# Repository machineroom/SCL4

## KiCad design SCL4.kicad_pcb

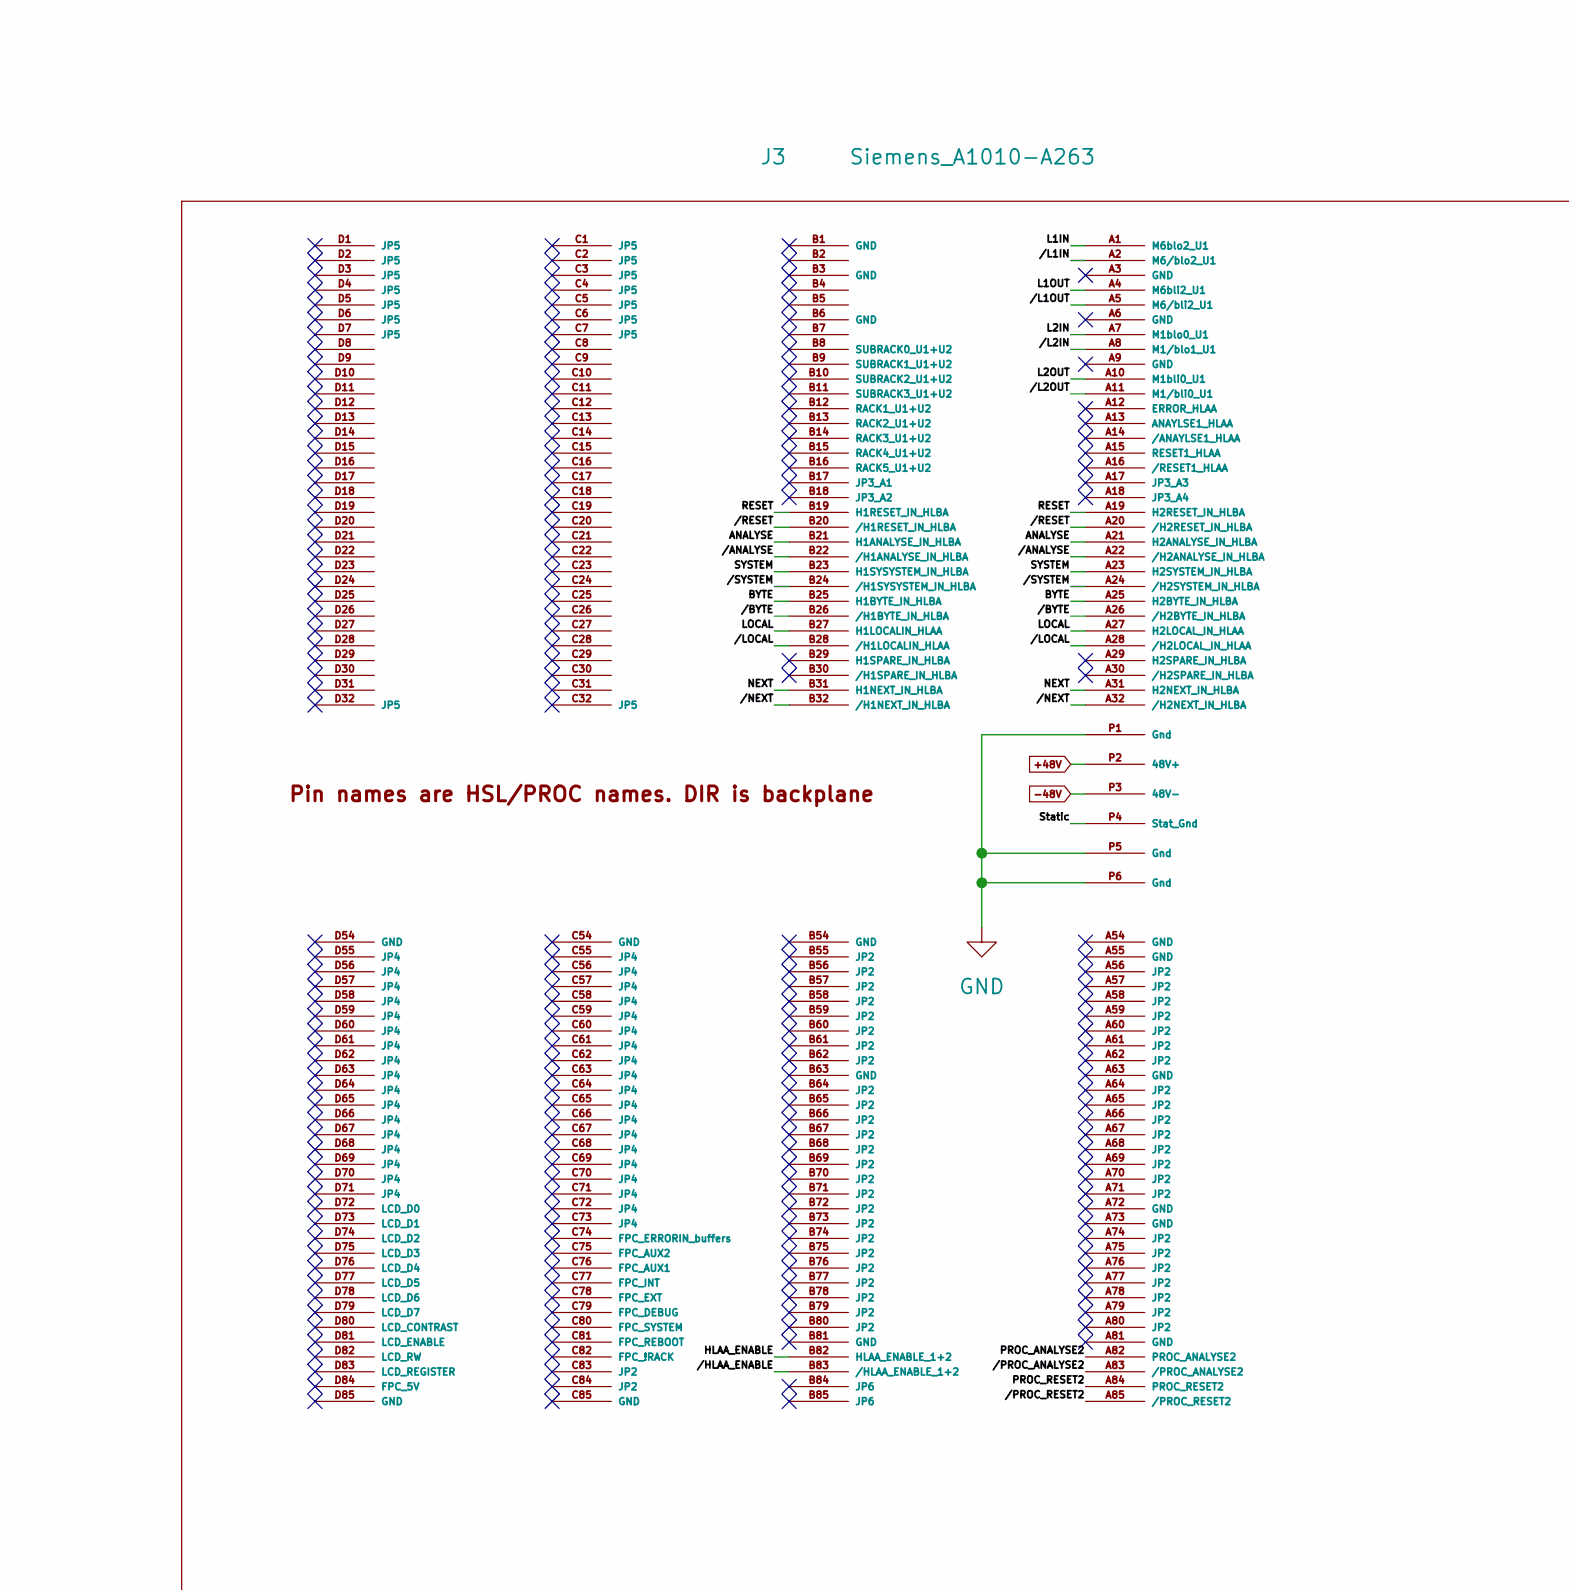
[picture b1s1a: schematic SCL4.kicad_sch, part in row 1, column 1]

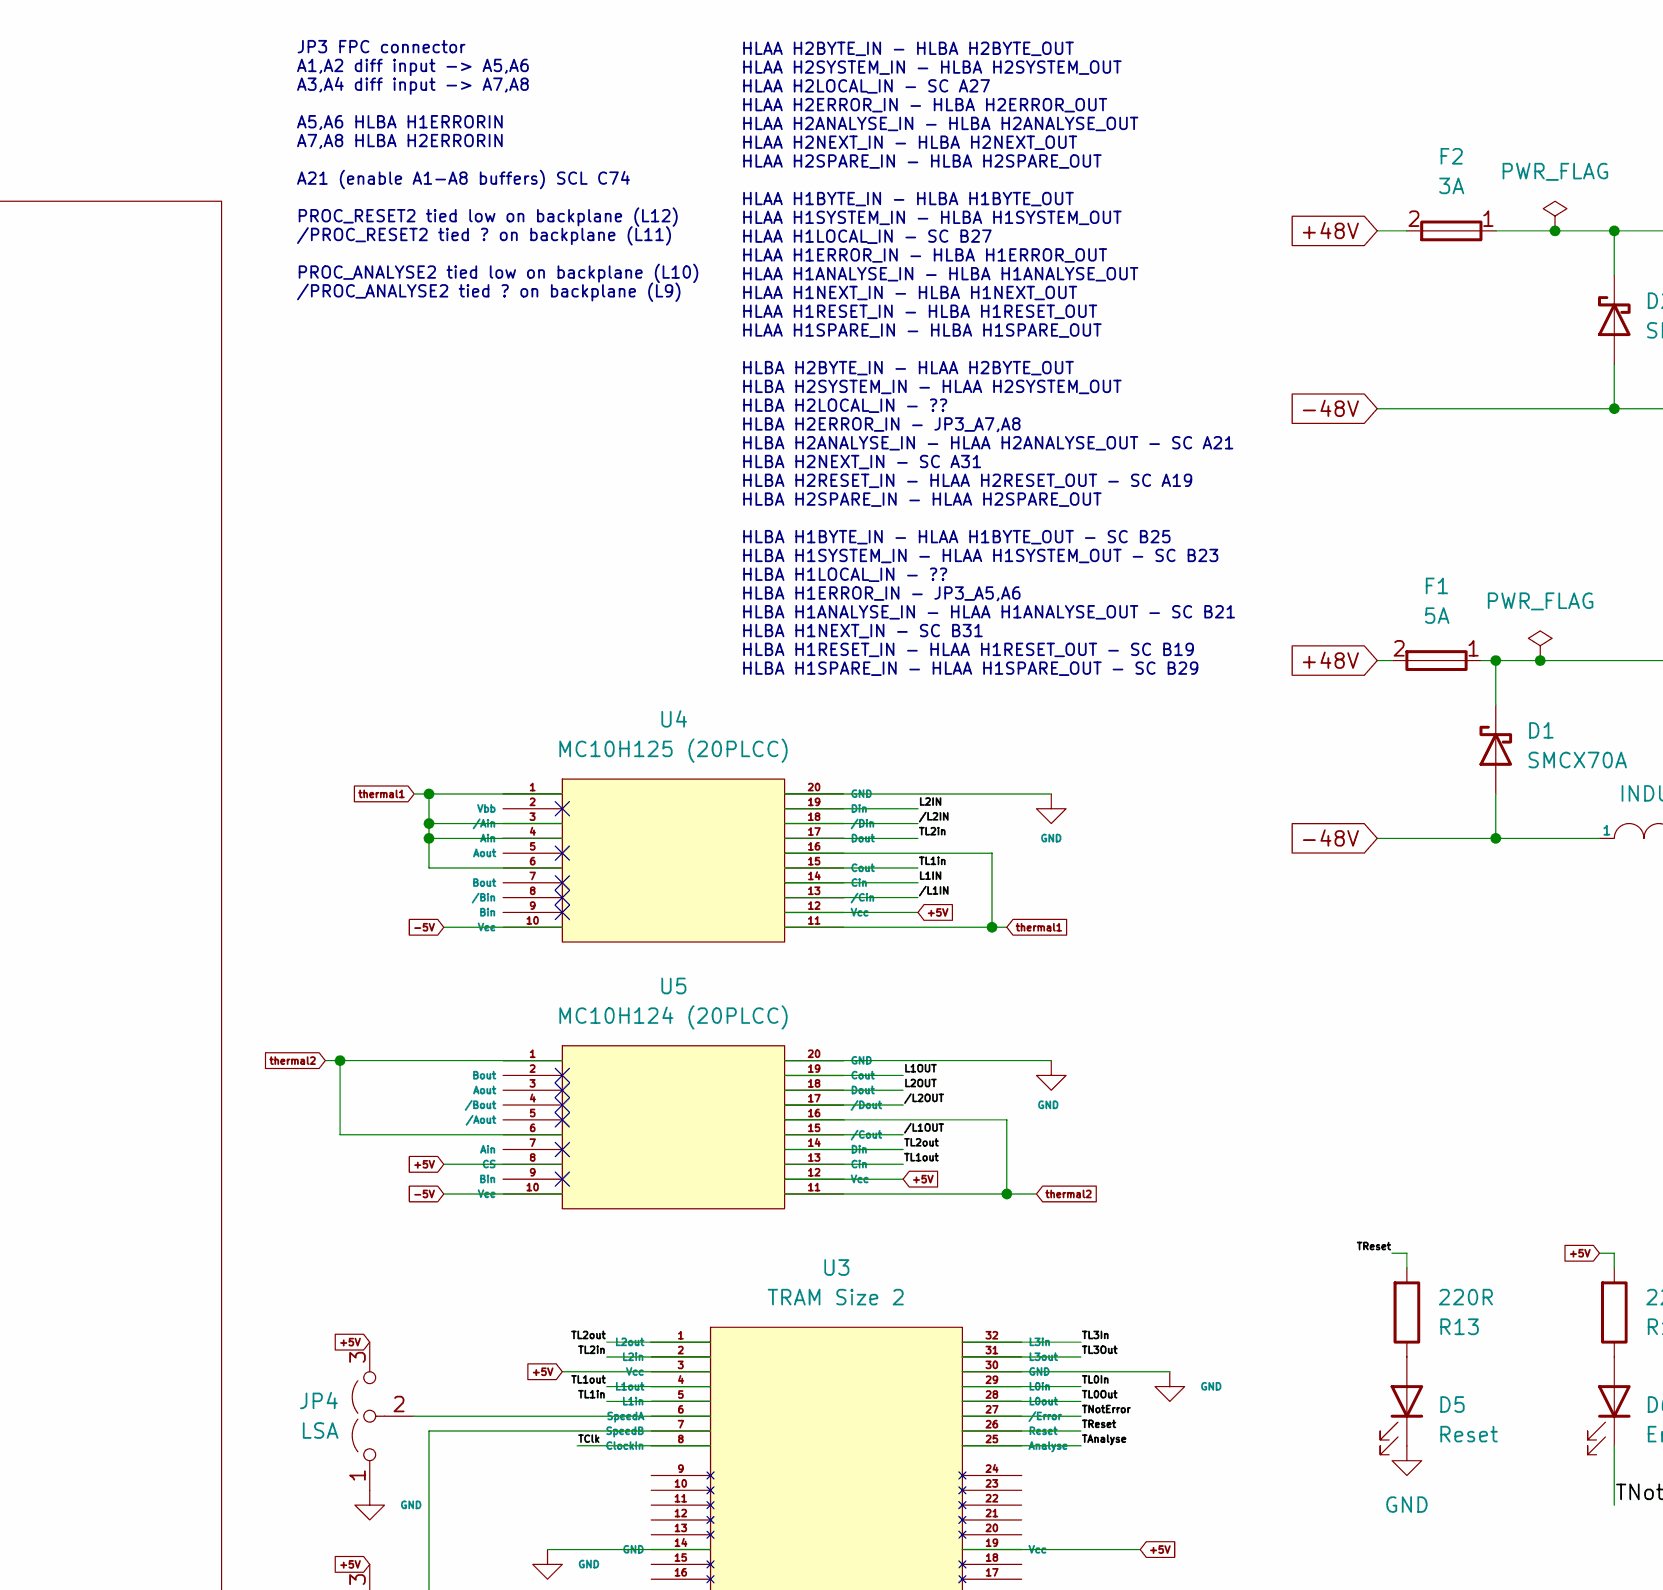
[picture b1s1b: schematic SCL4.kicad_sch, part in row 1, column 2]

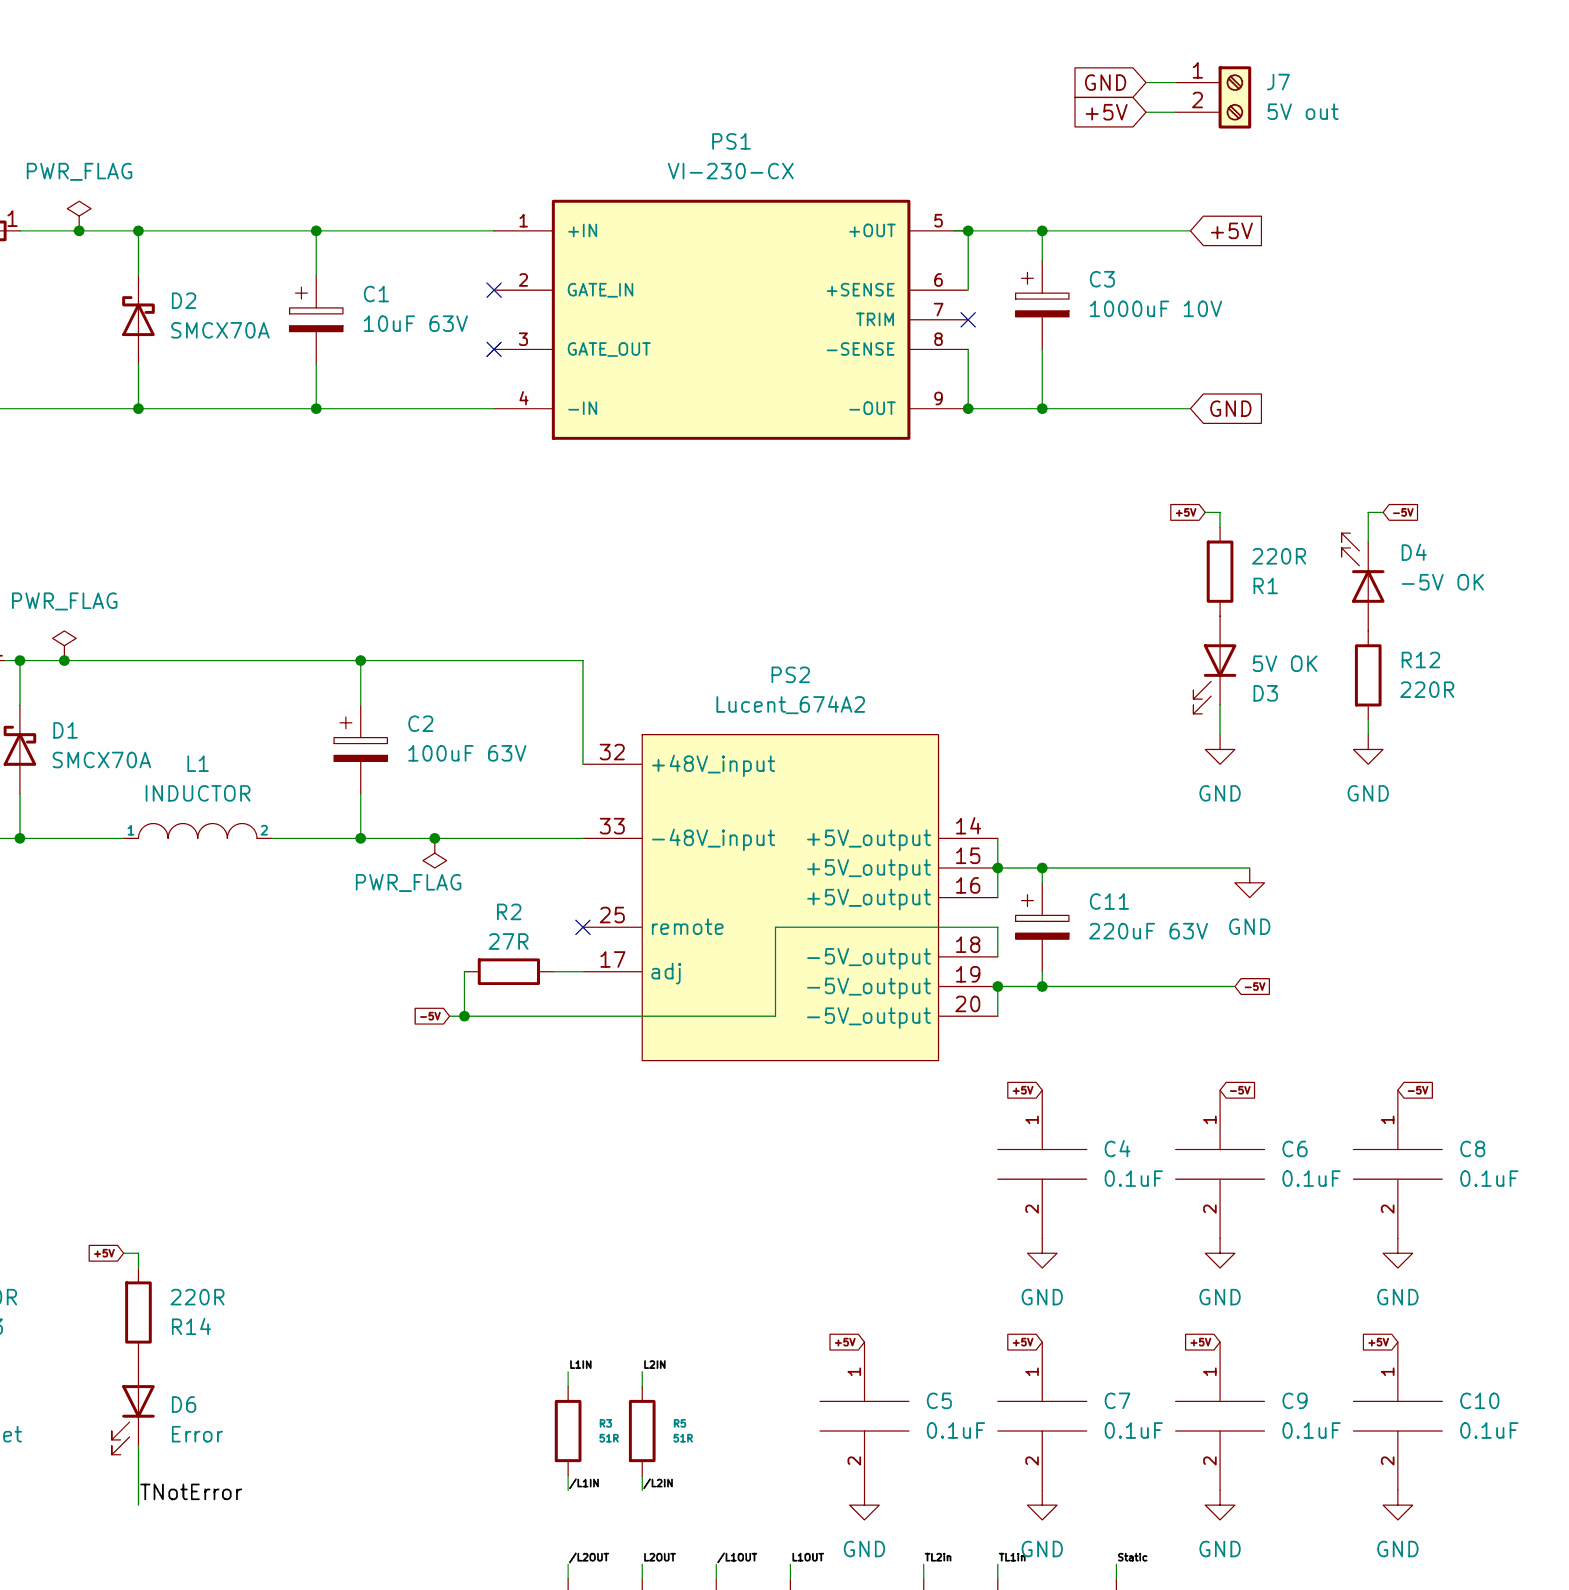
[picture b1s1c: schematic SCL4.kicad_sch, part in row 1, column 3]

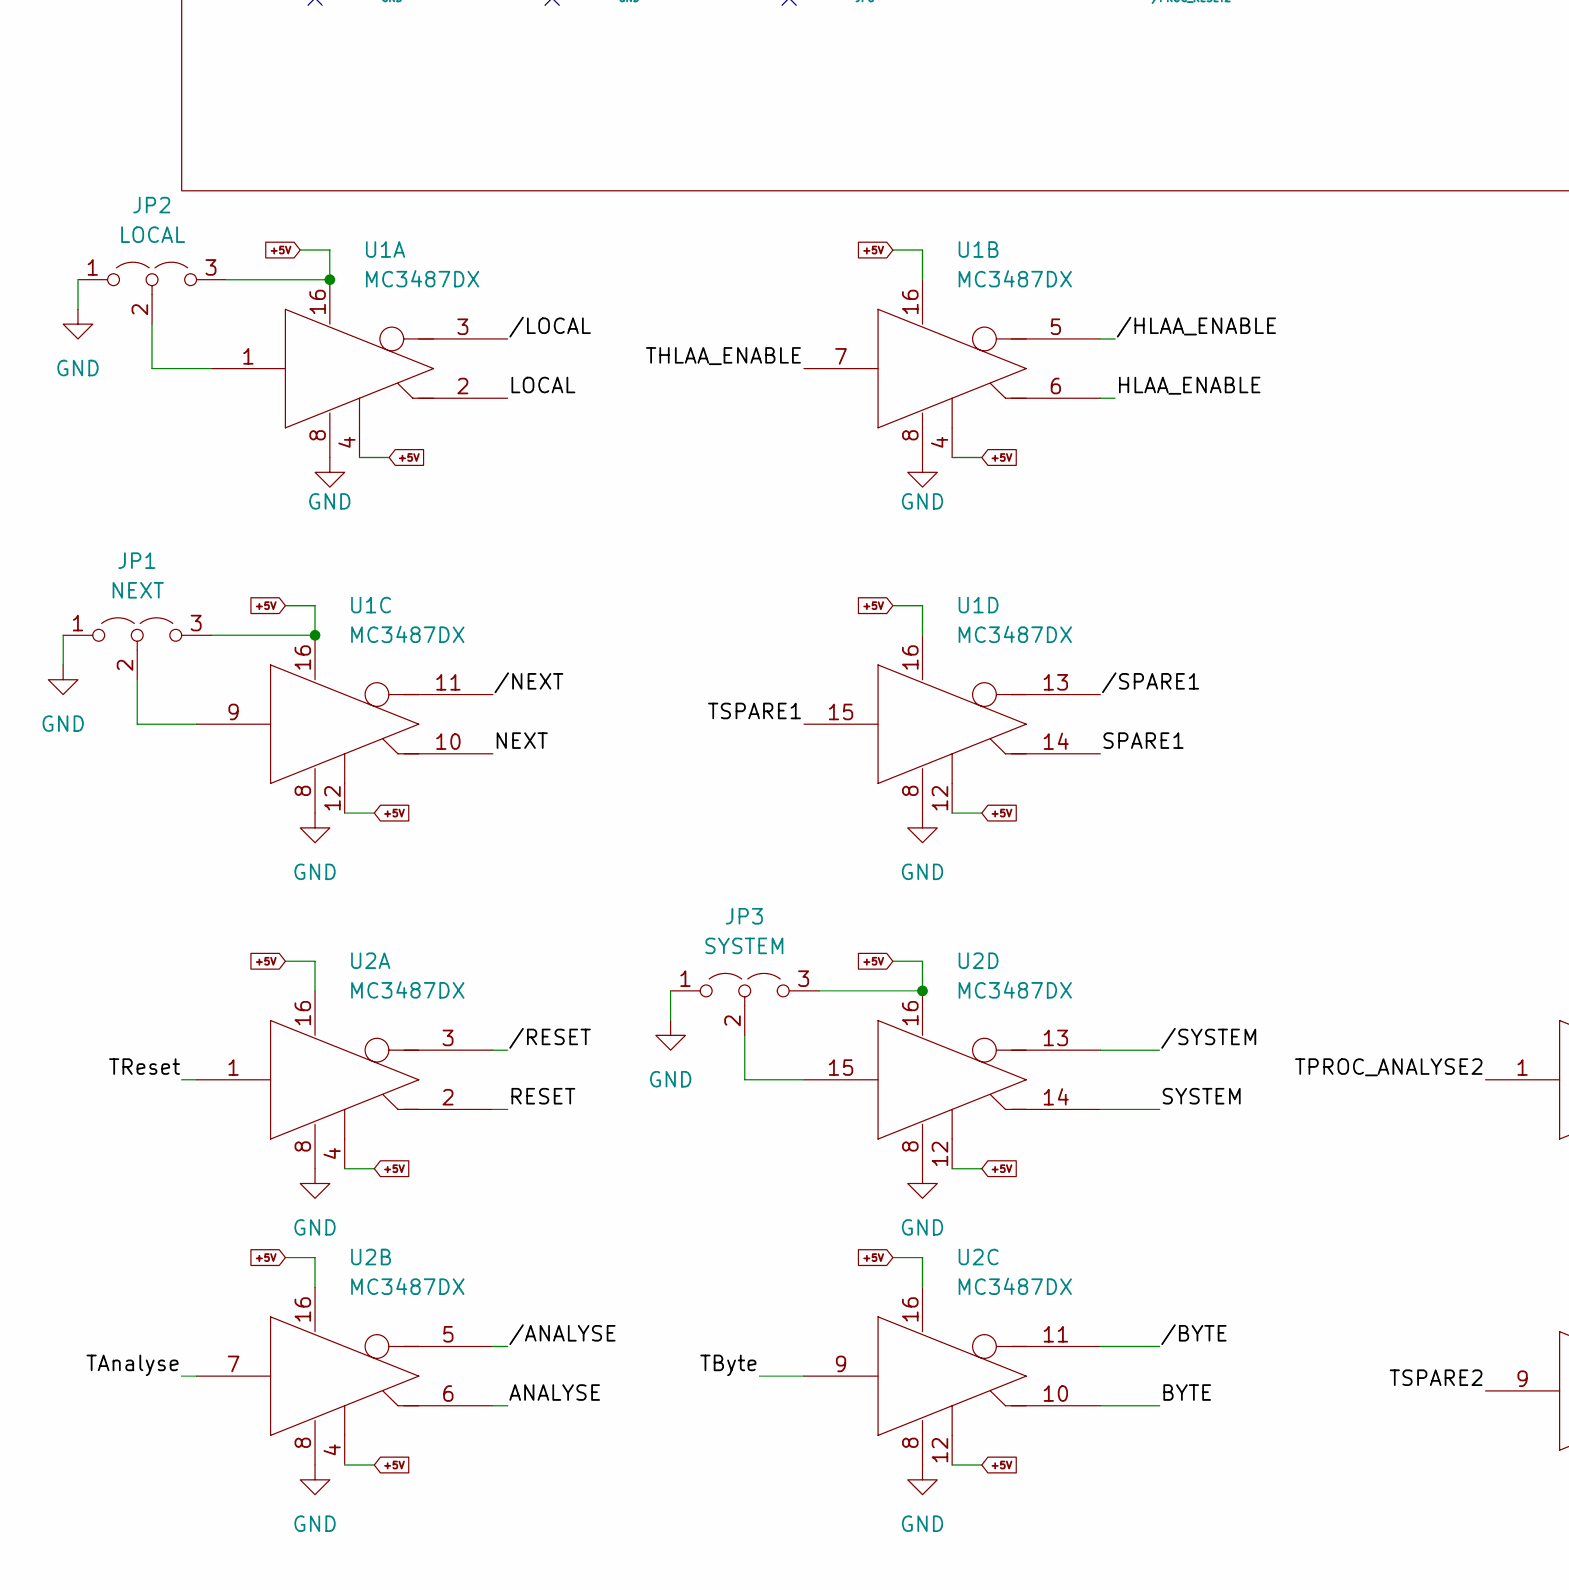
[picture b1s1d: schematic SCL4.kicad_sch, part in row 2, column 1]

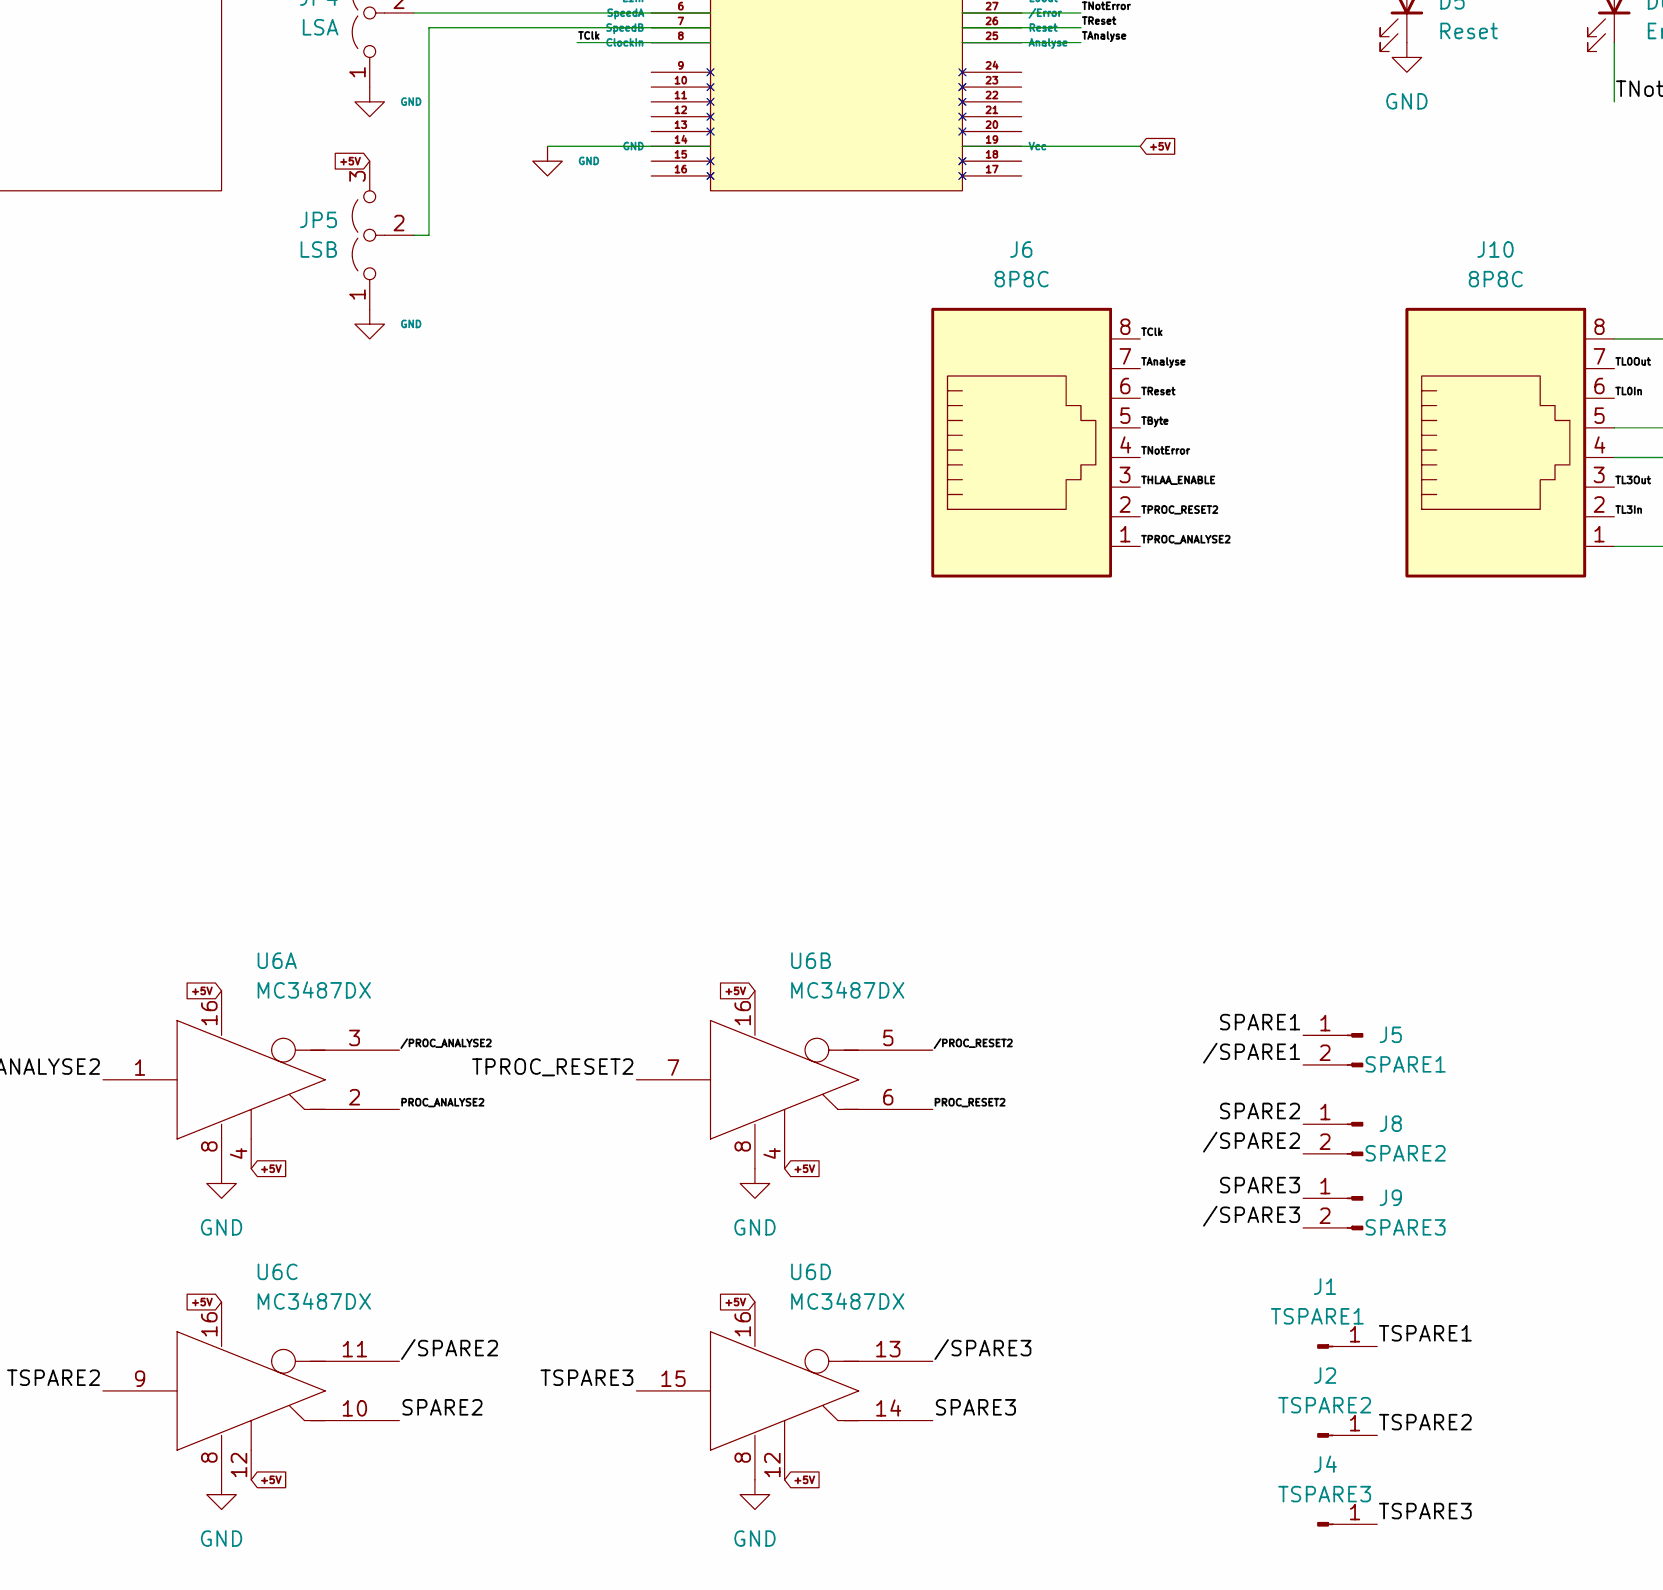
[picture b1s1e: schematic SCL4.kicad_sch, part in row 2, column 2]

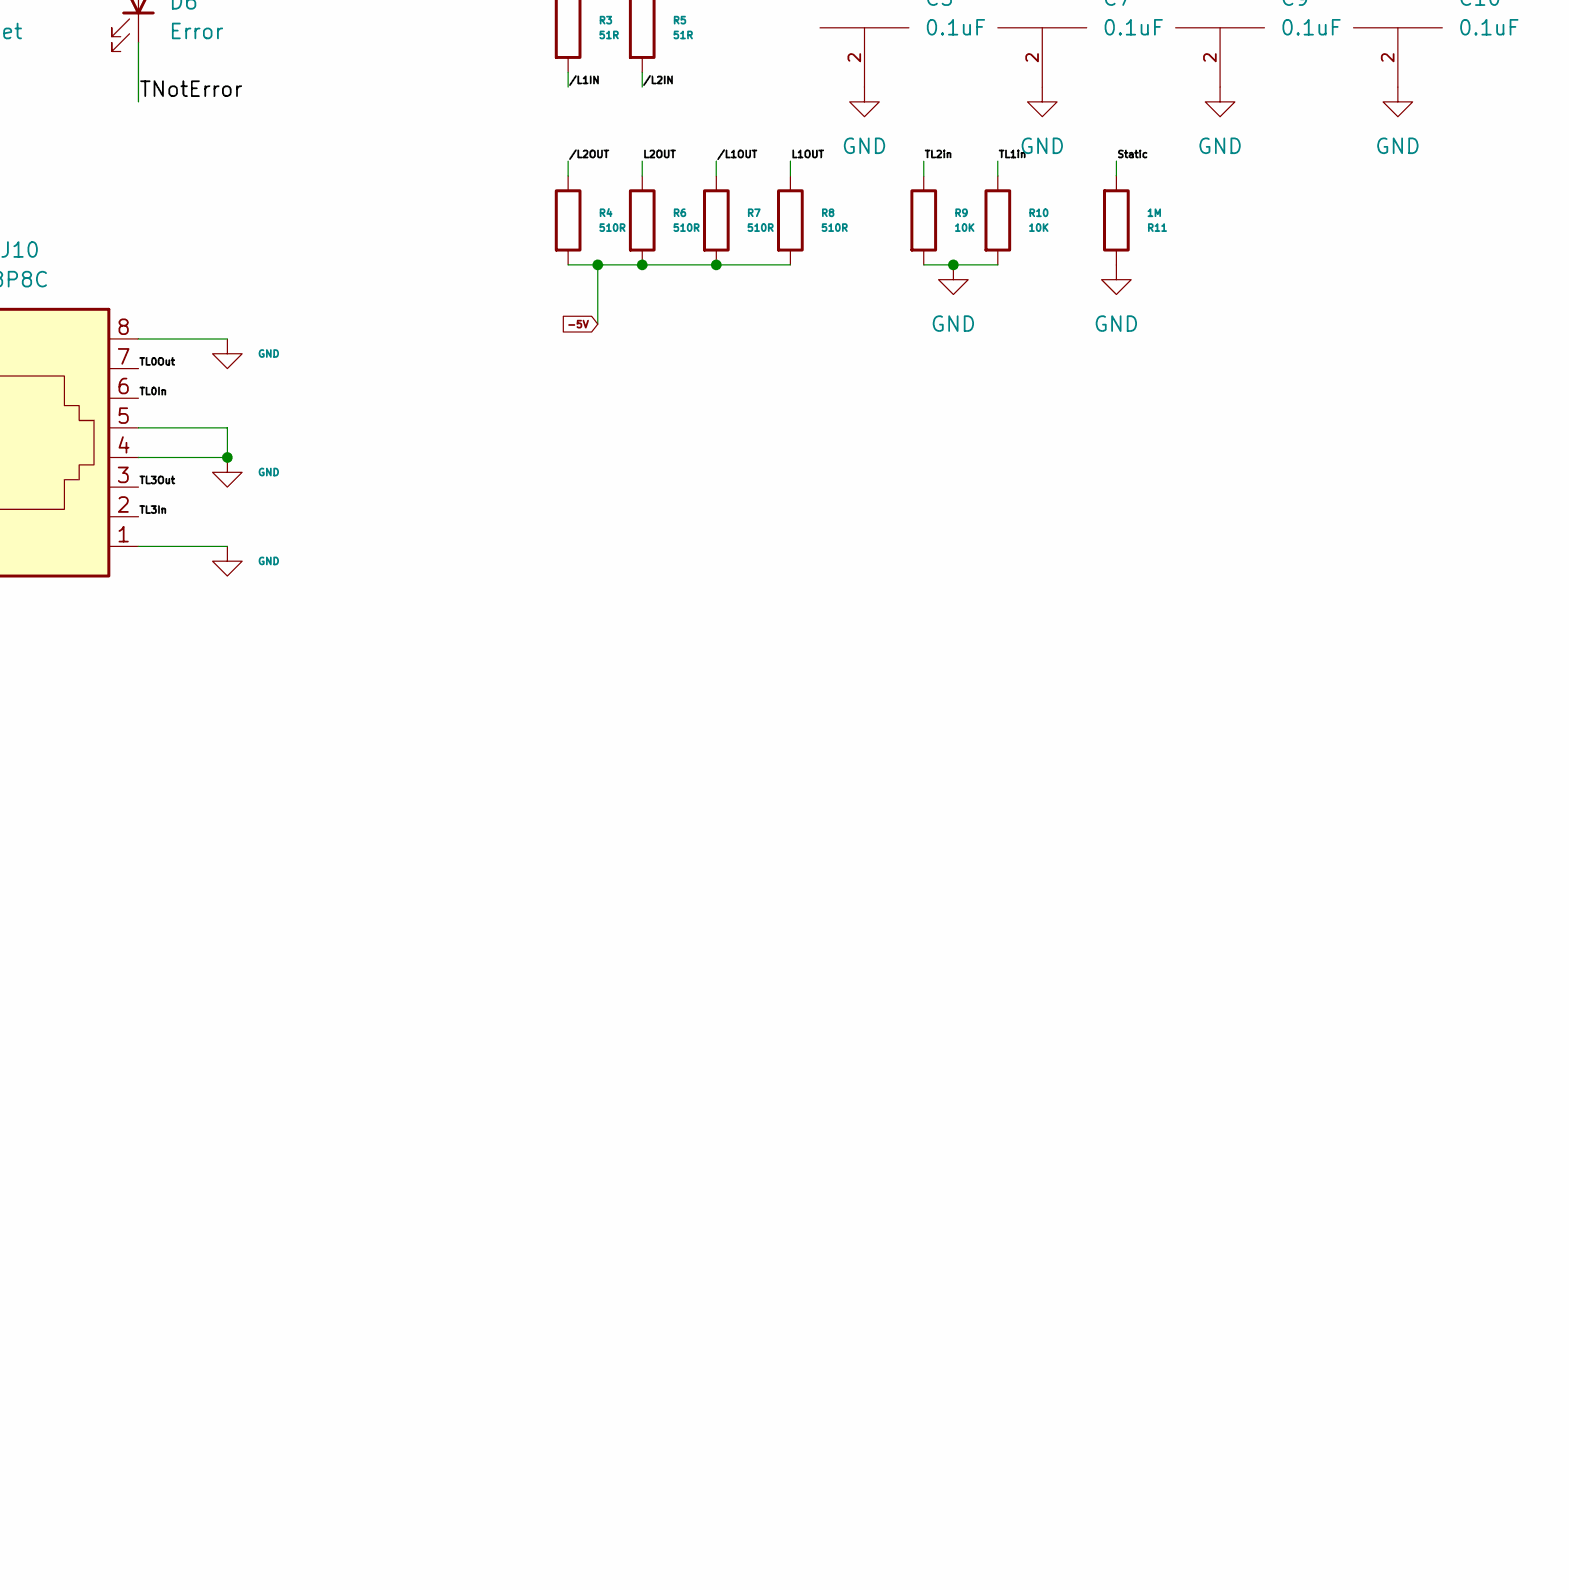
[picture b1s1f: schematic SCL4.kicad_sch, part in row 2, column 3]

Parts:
C1: 10uF 63V; CP_Radial_D5.0mm_P2.50mm
C2: 100uF 63V; CP_Radial_D10.0mm_P5.00mm
C3: 1000uF 10V; C_Radial_D12.5mm_H20.0mm_P5.00mm
C4, C5, C6, C7, C8, C9, C10: 0.1uF; C_0402_1005Metric_Pad0.74x0.62mm_HandSolder
C11: 220uF 63V; C_Radial_D8.0mm_H11.5mm_P3.50mm
D1, D2: SMCX70A; D_SMC_Handsoldering
D3: 5V OK; LED_Rectangular_W5.0mm_H2.0mm
D4: -5V OK; LED_Rectangular_W5.0mm_H2.0mm
D5: Reset; LED_Rectangular_W5.0mm_H2.0mm
D6: Error; LED_Rectangular_W5.0mm_H2.0mm
F1: 5A; BUSSMAN SFT-1
F2: 3A; BUSSMAN SFT-1
J1: TSPARE1; PinHeader_1x01_P2.54mm_Vertical
J2: TSPARE2; PinHeader_1x01_P2.54mm_Vertical
J3: Siemens_A1010-A263; Siedecon 256+6
J4: TSPARE3; PinHeader_1x01_P2.54mm_Vertical
J5: SPARE1; PinHeader_1x02_P2.54mm_Vertical
J6, J10: 8P8C; RJ45_Ninigi_GE
J7: 5V out; TerminalBlock_bornier-2_P5.08mm
J8: SPARE2; PinHeader_1x02_P2.54mm_Vertical
J9: SPARE3; PinHeader_1x02_P2.54mm_Vertical
JP1: NEXT; PinHeader_1x03_P2.54mm_Vertical
JP2: LOCAL; PinHeader_1x03_P2.54mm_Vertical
JP3: SYSTEM; PinHeader_1x03_P2.54mm_Vertical
JP4: LSA; PinHeader_1x03_P2.54mm_Vertical
JP5: LSB; PinHeader_1x03_P2.54mm_Vertical
L1: INDUCTOR; L_Axial_L12.8mm_D5.8mm_P20.32mm_Horizontal_Fastron_HBCC
PS1: VI-230-CX; vicor vi230cx; PARTREV 3.9
PS2: Lucent_674A2; Lucent 674A2
R1, R12, R13, R14: 220R; R_1206_3216Metric_Pad1.30x1.75mm_HandSolder
R2: 27R; R_1206_3216Metric_Pad1.30x1.75mm_HandSolder
R3, R5: 51R; R_1206_3216Metric_Pad1.30x1.75mm_HandSolder
R4, R6, R7, R8: 510R; R_1206_3216Metric_Pad1.30x1.75mm_HandSolder
R9, R10: 10K; R_1206_3216Metric_Pad1.30x1.75mm_HandSolder
R11: 1M; R_1206_3216Metric_Pad1.30x1.75mm_HandSolder
U1, U2, U6: MC3487DX; SOIC-16_3.9x9.9mm_P1.27mm
U3: TRAM Size 2; TRAM size 2
U4: MC10H125 (20PLCC); PLCC-20
U5: MC10H124 (20PLCC); PLCC-20

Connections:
+5V: C3.1, C4.1, C5.1, C7.1, C9.1, C10.1, J7.2, JP1.3 (B), JP2.3 (B), JP3.3 (B), JP4.3 (B), JP5.3 (B), PS1.5 (+OUT), PS1.6 (+SENSE), R1.2, R14.2, U1.4 (ENABLE), U1.12 (ENABLE), U1.16 (VCC), U2.4 (ENABLE), U2.12 (ENABLE), U2.16 (VCC), U3.3 (Vcc), U3.19 (Vcc), U4.12 (Vcc), U5.8 (CS), U5.12 (Vcc), U6.4 (ENABLE), U6.12 (ENABLE), U6.16 (VCC)
+48V: F1.2, F2.2, J3.P2 (48V+)
-5V: C6.1, C8.1, C11.2, D4.1 (K), PS2.18 (-5V_output), PS2.19 (-5V_output), PS2.20 (-5V_output), R2.2, R4.2, R6.2, R7.2, R8.2, U4.10 (Vee), U5.10 (Vee)
-48V: C1.2, D1.2 (A), D2.2 (A), J3.P3 (48V-), L1.1, PS1.4 (-IN)
/ANALYSE: J3.A21 (H2ANALYSE_IN_HLBA), J3.B21 (H1ANALYSE_IN_HLBA), U2.6 (OUT+)
/BYTE: J3.A25 (H2BYTE_IN_HLBA), J3.B25 (H1BYTE_IN_HLBA), U2.10 (OUT+)
/HLAA_ENABLE: J3.B82 (HLAA_ENABLE_1+2), U1.6 (OUT+)
/L1IN: J3.A1 (M6blo2_U1), R3.1, U4.14 (Cin)
/L1OUT: J3.A4 (M6bli2_U1), R8.1, U5.19 (Cout)
/L2IN: J3.A7 (M1blo0_U1), R5.1, U4.19 (Din)
/L2OUT: J3.A10 (M1bli0_U1), R6.1, U5.18 (Dout)
/LOCAL: J3.A27 (H2LOCAL_IN_HLAA), J3.B27 (H1LOCALIN_HLAA), U1.2 (OUT+)
/NEXT: J3.A31 (H2NEXT_IN_HLBA), J3.B31 (H1NEXT_IN_HLBA), U1.10 (OUT+)
/PROC_ANALYSE2: J3.A82 (PROC_ANALYSE2), U6.2 (OUT+)
/PROC_RESET2: J3.A84 (PROC_RESET2), U6.6 (OUT+)
/RESET: J3.A19 (H2RESET_IN_HLBA), J3.B19 (H1RESET_IN_HLBA), U2.2 (OUT+)
/SPARE1: J5.1, U1.14 (OUT+)
/SPARE2: J8.1, U6.10 (OUT+)
/SPARE3: J9.1, U6.14 (OUT+)
/SYSTEM: J3.A23 (H2SYSTEM_IN_HLBA), J3.B23 (H1SYSYSTEM_IN_HLBA), U2.14 (OUT+)
/Static: J3.P4 (Stat_Gnd), R11.2
/TAnalyse: J6.7, U2.7 (INPUT), U3.25 (Analyse)
/TByte: J6.5, U2.9 (INPUT)
/TClk: J6.8, U3.8 (ClockIn)
/THLAA_ENABLE: J6.3, U1.7 (INPUT)
/TL0In: J10.6, U3.29 (L0in)
/TL0Out: J10.7, U3.28 (L0out)
/TL1in: R10.1, U3.5 (L1in), U4.15 (Cout)
/TL1out: U3.4 (L1out), U5.13 (Cin)
/TL2in: R9.1, U3.2 (L2in), U4.17 (Dout)
/TL2out: U3.1 (L2out), U5.14 (Din)
/TL3In: J10.2, U3.32 (L3in)
/TL3Out: J10.3, U3.31 (L3out)
/TNotError: D6.1 (K), J6.4, U3.27 (/Error)
/TPROC_ANALYSE2: J6.1, U6.1 (INPUT)
/TPROC_RESET2: J6.2, U6.7 (INPUT)
/TReset: J6.6, R13.2, U2.1 (INPUT), U3.26 (Reset)
/TSPARE1: J1.1, U1.15 (INPUT)
/TSPARE2: J2.1, U6.9 (INPUT)
/TSPARE3: J4.1, U6.15 (INPUT)
//ANALYSE: J3.A22 (/H2ANALYSE_IN_HLBA), J3.B22 (/H1ANALYSE_IN_HLBA), U2.5 (OUT-)
//BYTE: J3.A26 (/H2BYTE_IN_HLBA), J3.B26 (/H1BYTE_IN_HLBA), U2.11 (OUT-)
//HLAA_ENABLE: J3.B83 (/HLAA_ENABLE_1+2), U1.5 (OUT-)
//L1IN: J3.A2 (M6/blo2_U1), R3.2, U4.13 (/Cin)
//L1OUT: J3.A5 (M6/bli2_U1), R7.1, U5.15 (/Cout)
//L2IN: J3.A8 (M1/blo1_U1), R5.2, U4.18 (/Din)
//L2OUT: J3.A11 (M1/bli0_U1), R4.1, U5.17 (/Dout)
//LOCAL: J3.A28 (/H2LOCAL_IN_HLAA), J3.B28 (/H1LOCALIN_HLAA), U1.3 (OUT-)
//NEXT: J3.A32 (/H2NEXT_IN_HLBA), J3.B32 (/H1NEXT_IN_HLBA), U1.11 (OUT-)
//PROC_ANALYSE2: J3.A83 (/PROC_ANALYSE2), U6.3 (OUT-)
//PROC_RESET2: J3.A85 (/PROC_RESET2), U6.5 (OUT-)
//RESET: J3.A20 (/H2RESET_IN_HLBA), J3.B20 (/H1RESET_IN_HLBA), U2.3 (OUT-)
//SPARE1: J5.2, U1.13 (OUT-)
//SPARE2: J8.2, U6.11 (OUT-)
//SPARE3: J9.2, U6.13 (OUT-)
//SYSTEM: J3.A24 (/H2SYSTEM_IN_HLBA), J3.B24 (/H1SYSYSTEM_IN_HLBA), U2.13 (OUT-)
GND: C3.2, C4.2, C5.2, C6.2, C7.2, C8.2, C9.2, C10.2, C11.1, D3.1 (K), D5.1 (K), J3.P1 (Gnd), J3.P5 (Gnd), J3.P6 (Gnd), J7.1, J10.1, J10.4, J10.5, J10.8, JP1.1 (A), JP2.1 (A), JP3.1 (A), JP4.1 (A), JP5.1 (A), PS1.8 (-SENSE), PS1.9 (-OUT), PS2.14 (+5V_output), PS2.15 (+5V_output), PS2.16 (+5V_output), R9.2, R10.2, R11.1, R12.2, U1.8 (GND), U2.8 (GND), U3.14 (GND), U3.30 (GND), U4.20 (GND), U5.20 (GND), U6.8 (GND)
unnamed: C1.1, D2.1 (K), F2.1, PS1.1 (+IN)
unnamed: C2.1, D1.1 (K), F1.1, PS2.32 (+48V_input)
unnamed: C2.2, L1.2, PS2.33 (-48V_input)
unnamed: D3.2 (A), R1.1
unnamed: D4.2 (A), R12.1
unnamed: D5.2 (A), R13.1
unnamed: D6.2 (A), R14.1
unnamed: JP1.2 (C), U1.9 (INPUT)
unnamed: JP2.2 (C), U1.1 (INPUT)
unnamed: JP3.2 (C), U2.15 (INPUT)
unnamed: JP4.2 (C), U3.6 (SpeedA)
unnamed: JP5.2 (C), U3.7 (SpeedB)
unnamed: PS2.17 (adj), R2.1
thermal1: U4.1, U4.3 (/Ain), U4.4 (Ain), U4.6, U4.11, U4.16
thermal2: U5.1, U5.6, U5.11, U5.16

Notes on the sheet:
JP3 FPC connector A1,A2 diff input -> A5,A6 A3,A4 diff input -> A7,A8 A5,A6 HLBA H1ERRORIN A7,A8 HLBA H2ERRORIN A21 (enable A1-A8 buffers) SCL C74 PROC_RESET2 tied low on backplane (L12) /PROC_RESET2 tied ? on backplane (L11) PROC_ANALYSE2 tied low on backplane (L10) /PROC_ANALYSE2 tied ? on backpl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
HLAA H2BYTE_IN - HLBA H2BYTE_OUT HLAA H2SYSTEM_IN - HLBA H2SYSTEM_OUT HLAA H2LOCAL_IN - SC A27 HLAA H2ERROR_IN - HLBA H2ERROR_OUT HLAA H2ANALYSE_IN - HLBA H2ANALYSE_OUT HLAA H2NEXT_IN - HLBA H2NEXT_OUT HLAA H2SPARE_IN - HLBA H2SPARE_OUT HLAA H1BYTE_IN - HLBA H1BYTE_OUT HLAA H1SYSTEM_IN - HLBA H1SYS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

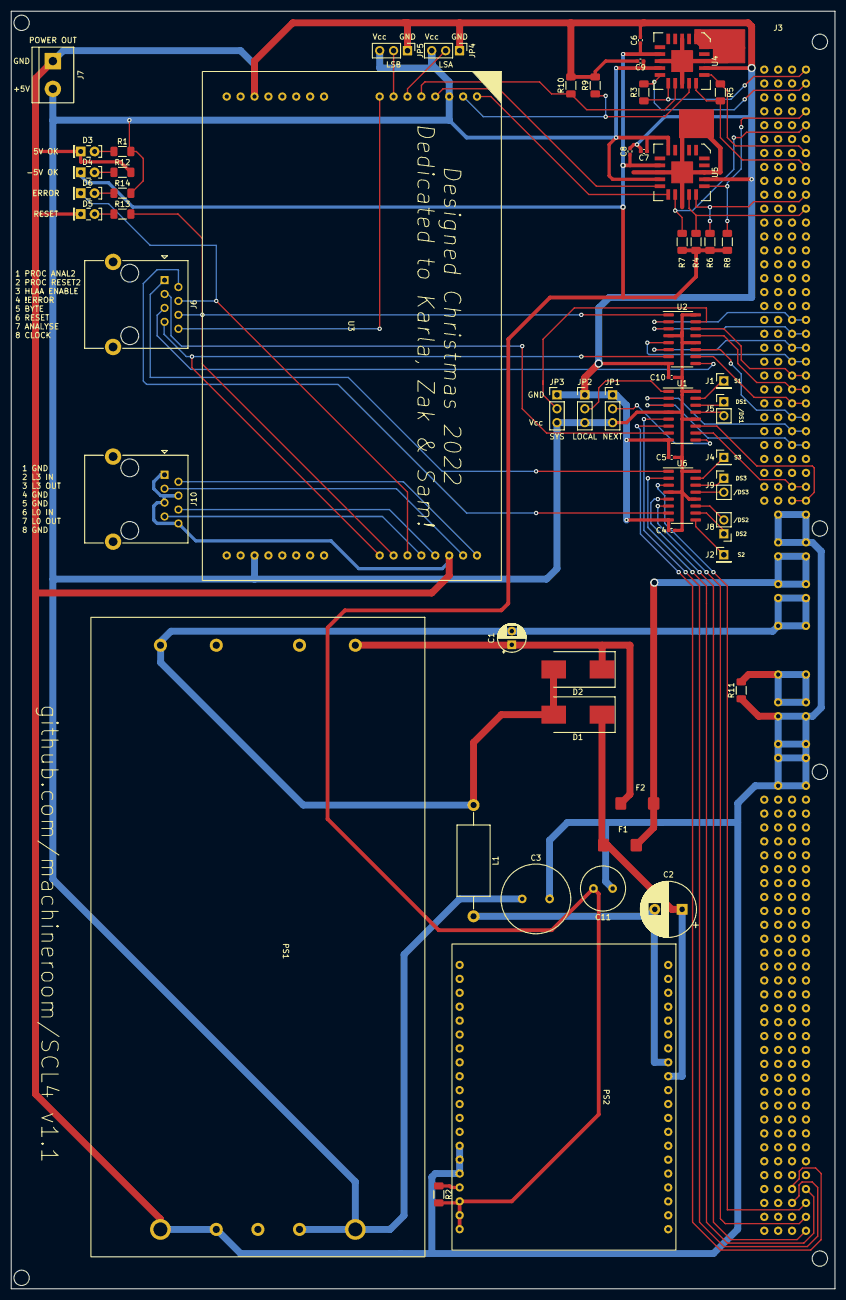
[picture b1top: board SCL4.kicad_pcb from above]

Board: 2 copper layers, 150.5 x 233.3 mm, 57 parts (0 on the bottom side), 72 nets.

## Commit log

2022-09-23 siedecon in good shape
2022-09-24 ERC passes
2022-09-24 missing files
2022-09-25 swap abcd on siedecon
2022-09-25 footprint for TRAM and siedecon
2022-09-25 stuff
2022-09-25 fp assignment
2022-09-25 odd ball SMD fuses
2022-09-25 starting routing
2022-10-09 board layout complete
2022-10-09 fix static gnd pin
2022-10-09 polish
2022-10-15 vicor ds
2022-10-15 fix pin numbering of vicor
2022-10-15 correct differential orientation
2022-10-15 fixup tram pin spacing
2022-10-15 correct pin spacing of vi230cx
2022-10-16 Correct silkscreen labels
2022-10-16 update 256pin connector
2022-10-16 set output dir
2022-10-22 more SCL pins named
2022-11-11 Add HLAA enable jumper
2022-12-31 Major rework - fix -5V2 PSU orientation - analyse2 & reset2 signals for proc only operation (no HSL) - bring TRAM L1 and L3 to external header - lay down C3 to reduce height - decoupling - reduce + b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
2023-01-01 Use RJ45 external and add thermal pads
2023-01-01 Add extraction holes
2023-01-01 more LEDs
2023-01-01 tidy
2023-01-14 fix pins for -5V calibration R
